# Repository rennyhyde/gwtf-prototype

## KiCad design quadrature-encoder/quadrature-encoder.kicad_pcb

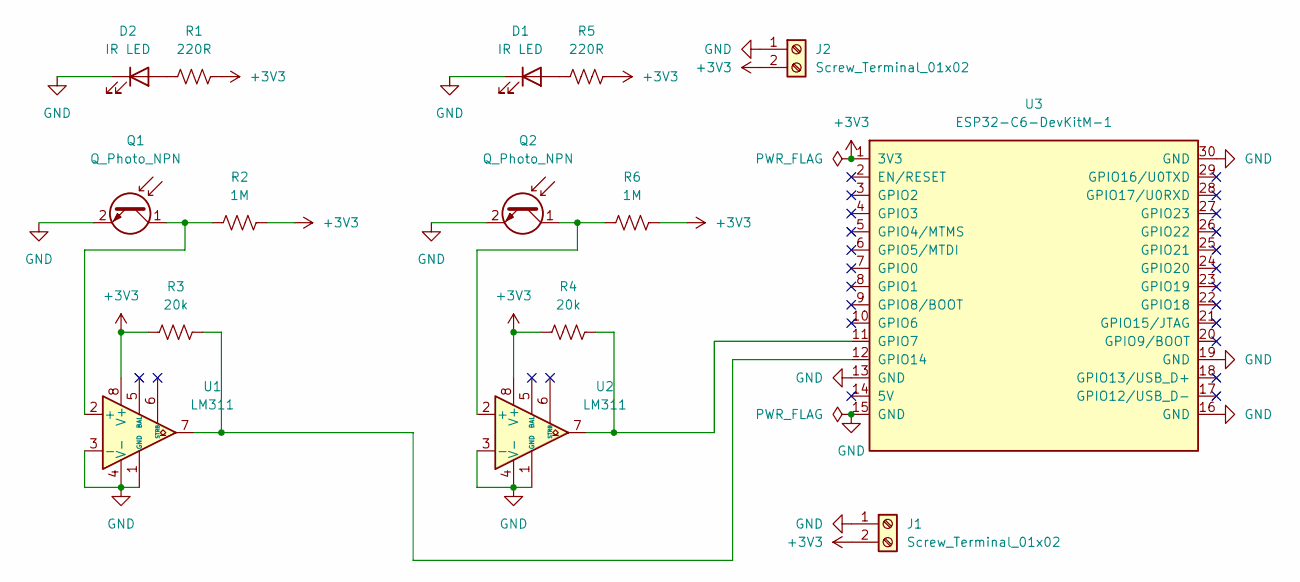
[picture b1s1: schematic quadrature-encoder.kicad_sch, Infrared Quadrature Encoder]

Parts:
D1, D2: IR LED; CR_S7100_VIS
J1, J2: Screw_Terminal_01x02; ScrewTerminal_1x02_P3.5mm_Blue
Q1, Q2: Q_Photo_NPN; LED_TEMD1000
R1, R5: 220R; R_0201_0603Metric
R2, R6: 1M; R_0201_0603Metric
R3, R4: 20k; R_0201_0603Metric
U1, U2: LM311; D8
U3: ESP32-C6-DevKitM-1

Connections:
+3V3: J1.2, J2.2, R1.2, R2.2, R3.1, R4.1, R5.2, R6.2, U1.8 (V+), U2.8 (V+), U3.1 (3V3)
GND: D1.1 (K), D2.1 (K), J1.1, J2.1, Q1.2 (E), Q2.2 (E), U1.1 (GND), U1.3 (-), U1.4 (V-), U2.1 (GND), U2.3 (-), U2.4 (V-), U3.13 (GND), U3.15 (GND), U3.16 (GND), U3.19 (GND), U3.30 (GND)
unnamed: D1.2 (A), R5.1
unnamed: D2.2 (A), R1.1
unnamed: Q1.1 (C), R2.1, U1.2 (+)
unnamed: Q2.1 (C), R6.1, U2.2 (+)
unnamed: R4.2, U2.7, U3.11 (GPIO7)
unnamed: R3.2, U1.7, U3.12 (GPIO14)

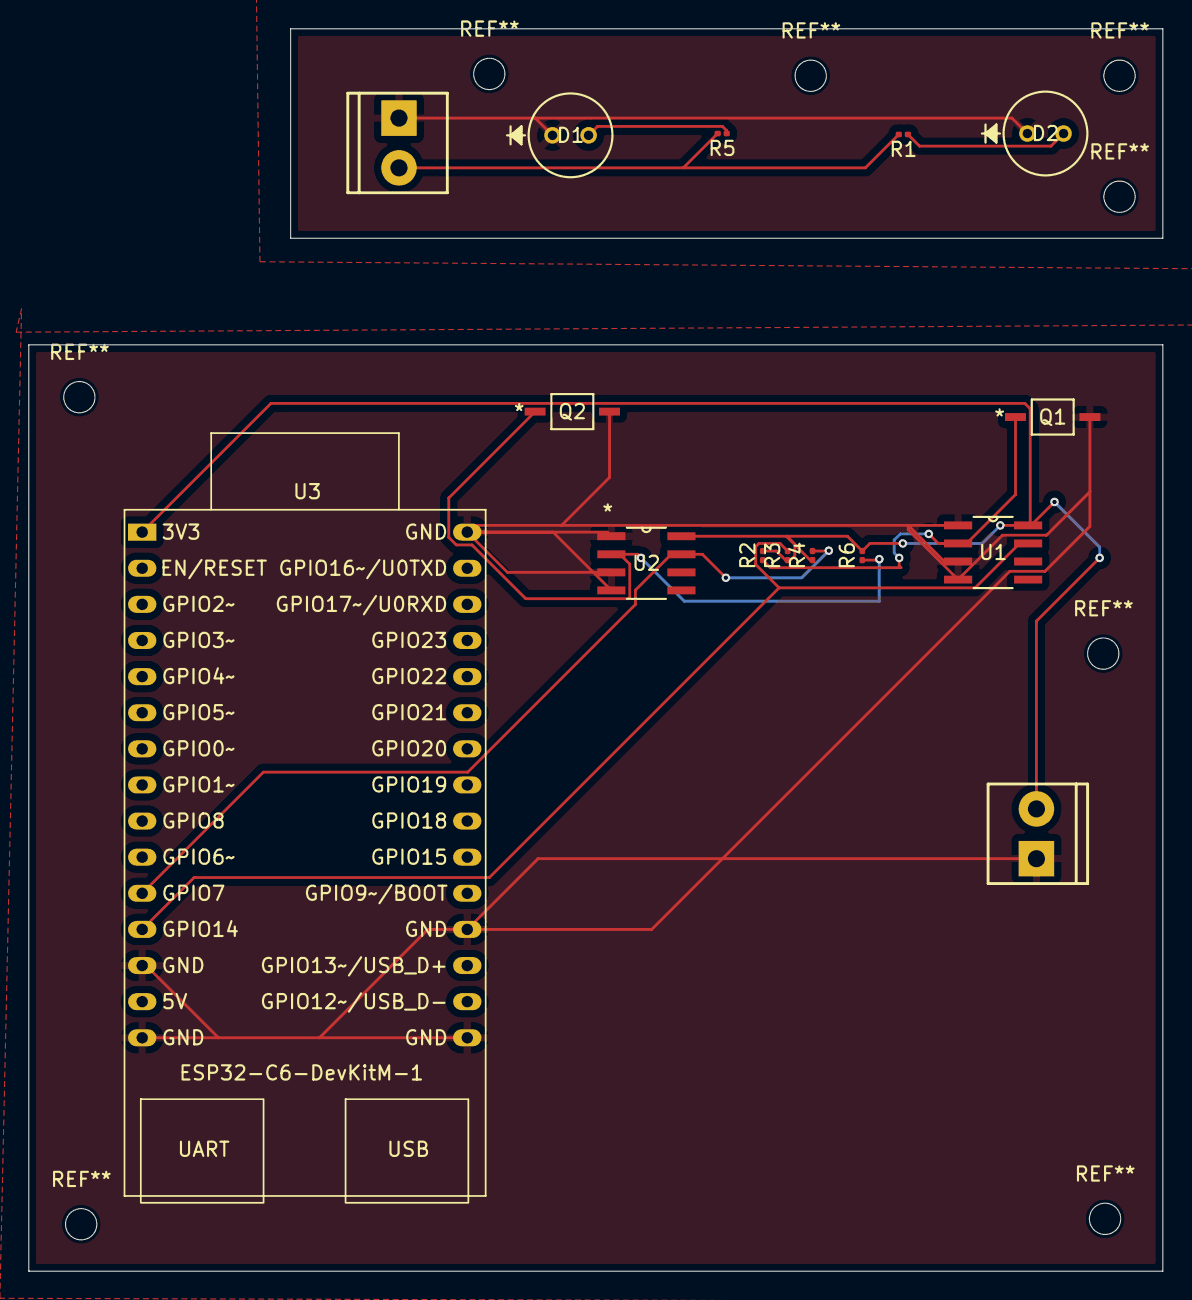
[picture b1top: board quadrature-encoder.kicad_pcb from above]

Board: 2 copper layers, 79.8 x 87.4 mm, 15 parts (0 on the bottom side), 8 nets.

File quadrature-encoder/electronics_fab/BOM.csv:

Designator,Qty,Value,Description,Footprint,Manufacturer,MPN,Digikey Part No (Cut Tape),Unit Price (1),Unit Price (10),Extended Price (1ea),Digikey URL
D1 D2,2,IR LED,IR Emitter 950nm 10deg TO-18,swimon:CR_S7100_VIS,Vishay Semiconductor,TSTS7100,TSTS7100-ND,$4.64,$3.44,$9.28,https://www.digikey.com/en/products/detail/vishay-semiconduc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
Q1 Q2,2,Q_Photo_NPN,Phototransistor 950nm 2-SMD Z-Bend,swimon:LED_TEMD1000,Vishay Semiconductor,TEMT1000,751-1052-1-ND,$0.90,$0.63,$1.80,https://www.digikey.com/en/products/detail/vishay-semiconduc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
U1 U2,2,LM311,Voltage Comparator General Purpose 8-SOIC,swimon:D8,Texas Instruments,LM311DR,296-1388-1-ND,$0.26,$0.18,$0.52,https://www.digikey.com/en/products/detail/texas-instruments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
U3,1,ESP32-C6-DevKitM-1,ESP32-C6 Wi-Fi/BT Dev Board (4MB flash),PCM_Espressif:ESP32-C6-DevKitM-1,Espressif Systems,ESP32-C6-DEVKITM-1-N4,1965-ESP32-C6-DEVKITM-1-N4-ND,$8.00,—,$8.00,https://www.digikey.com/en/products/detail/espressif-systems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
R1 R5,2,220R,Res 220 Ohm 5% 1/20W SMD 0201,Resistor_SMD:R_0201_0603Metric,Yageo,RC0201JR-07220RL,311-220NCT-ND,$0.10,$0.03,$0.20,https://www.digikey.com/en/products/detail/yageo/RC0201JR-07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
R2 R6,2,1M,Res 1M Ohm 1% 1/20W SMD 0201,Resistor_SMD:R_0201_0603Metric,Yageo,RC0201FR-071ML,311-1MMCT-ND,$0.10,$0.03,$0.20,https://www.digikey.com/en/products/detail/yageo/RC0201FR-07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
R3 R4,2,20k,Res 20K Ohm 1% 1/20W SMD 0201,Resistor_SMD:R_0201_0603Metric,Yageo,RC0201FR-0720KL,YAG2276CT-ND,$0.10,$0.03,$0.20,https://www.digikey.com/en/products/detail/yageo/RC0201FR-07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
"J2, J1",2,Screw_Terminal_01x02,2-Pos Wire-to-Board Terminal Block 3.5mm PTH,SparkFun-Connector:ScrewTerminal_1x02_P3.5mm_Blue,On Shore Technology,OSTTE020161,ED2635-ND,$0.67,$0.50,$0.67,https://www.digikey.com/en/products/detail/on-shore-technolo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
,,,,,,,,,,Total (qty 1 each):,$20.87

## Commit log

2026-04-27 init commit
2026-04-27 Fix weird dependency issues
2026-04-27 update serial dev paths
2026-04-28 fixed serial path bug
2026-04-28 more bugs
2026-04-28 trying
2026-04-28 Try only one tank
2026-04-28 add startup script
2026-04-28 add autostart script
2026-04-28 fix web addr
2026-04-28 logging for server
2026-04-28 bypass prod server check
2026-04-28 updated GUI
2026-04-28 fixed scrolling bug
